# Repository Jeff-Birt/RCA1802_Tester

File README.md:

# RCA1802_Tester
Using an Aruino Mega 2560 to test RCA/Harris/Intersil 1802 processors

I boughtt a batch of old RCA 1802 micro-processors from C.H. Ina & Company on eBay. When they showed up it was obvious that had been sanded and re-labeled. The rest of the parts for the project I wanted them for had not arrived and I wanted to test them before complaining.

I had an Arduino Mega 2560 sitting on the bench and thought I would try to use it to test the 1802s. This project is the result of that effort...

NOTE:
 PCB Design, button handling code, and EF randomization code from: Hans Liss, Thanks Hans!

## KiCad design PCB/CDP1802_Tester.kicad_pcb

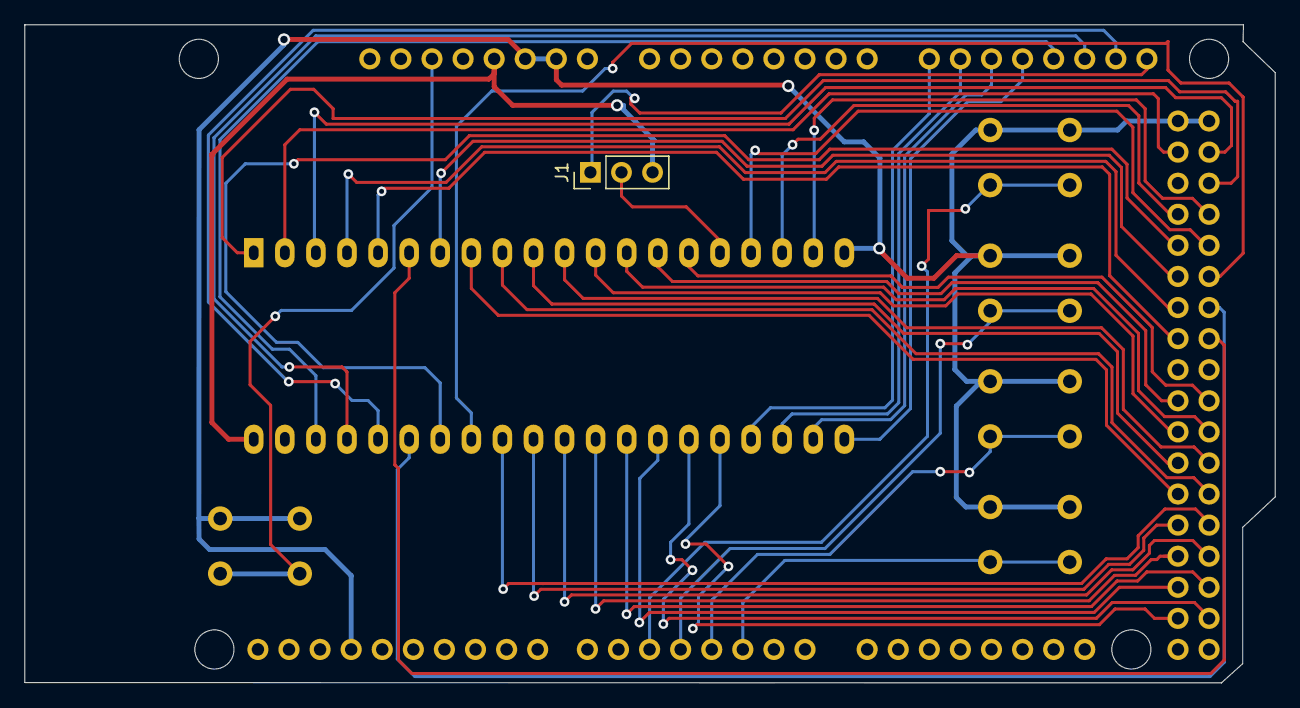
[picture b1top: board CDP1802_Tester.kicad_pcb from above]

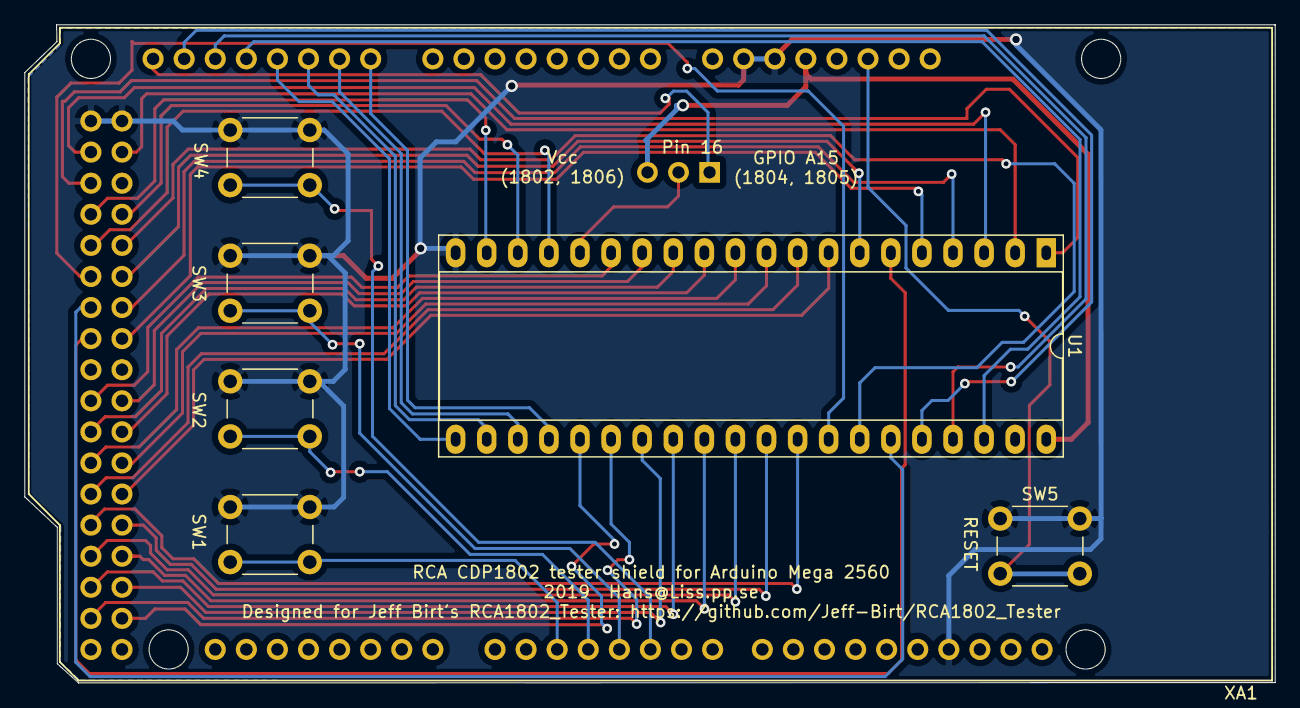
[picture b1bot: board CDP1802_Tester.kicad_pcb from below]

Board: 2 copper layers, 102.2 x 53.8 mm, 8 parts (7 on the bottom side), 45 nets.

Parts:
J1: Conn_01x03; Pin_Header_Straight_1x03_Pitch2.54mm
SW1, SW2, SW3, SW4, SW5: SW_Push; SW_PUSH_6mm
U1: CDP1802ACE; DIP-40_W15.24mm_Socket_ZIF
XA1: Arduino_Mega2560_Shield_alt1

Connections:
/CLEAR: U1.3, XA1.D53
/CLOCK: U1.1, XA1.D51
/D0: U1.15, XA1.D37
/D1: U1.14, XA1.D36
/D2: U1.13, XA1.D35
/D3: U1.12, XA1.D34
/D4: U1.11, XA1.D33
/D5: U1.10, XA1.D32
/D6: U1.9, XA1.D31
/D7: U1.8, XA1.D30
/DMA_IN: U1.38, XA1.A12
/DMA_OUT: U1.37, XA1.A13
/EF1: U1.24, XA1.A8
/EF2: U1.23, XA1.A9
/EF3: U1.22, XA1.A10
/EF4: U1.21, XA1.A11
/INTERRUPT: U1.36, XA1.A14
/MA0: U1.25, XA1.D22
/MA1: U1.26, XA1.D23
/MA2: U1.27, XA1.D24
/MA3: U1.28, XA1.D25
/MA4: U1.29, XA1.D26
/MA5: U1.30, XA1.D27
/MA6: U1.31, XA1.D28
/MA7: U1.32, XA1.D29
/MRD: U1.7, XA1.D44
/MWR: U1.35, XA1.D43
/N0: U1.19, XA1.D49
/N1: U1.18, XA1.D48
/N2: U1.17, XA1.D47
/Q: U1.4, XA1.D42
/SC0: U1.6, XA1.D41
/SC1: U1.5, XA1.D40
/TPA: U1.34, XA1.D46
/TPB: U1.33, XA1.D45
/WAIT: U1.2, XA1.D52
GND: SW1.2, SW2.2, SW3.2, SW4.2, SW5.1, U1.20, XA1.GND1, XA1.GND2, XA1.GND3, XA1.GND5, XA1.GND6
unnamed: J1.1, XA1.A15
unnamed: J1.2, U1.16
unnamed: SW1.1, XA1.D2
unnamed: SW2.1, XA1.D3
unnamed: SW3.1, XA1.D4
unnamed: SW4.1, XA1.D5
unnamed: SW5.2, XA1.RST1
VCC: J1.3, U1.40, XA1.5V1

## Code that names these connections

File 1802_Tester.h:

#pragma once

// PORT A (inputs to Arduino)
#define ADD_BUS		0xFF	// well, the address bus of course

// PORT B (Outputs from Arduino)
// /CLEAR	/WAIT	MODE (1802)
//	L		L		LOAD
//	L		H		RESET
//	H		L		PAUSE
//	H		H		RUN
#define CLEAR		0x01	// active low
#define WAIT		0x02	// active Low
#define CLOCK		0x04	// Clock input, active low

// PORT C (bi-directional)
#define DATA_BUS	0xFF	// well, the data bus of course

//PORT G (inputs to Arduino)
#define SC0			0x01	// SC0==0->Fetch, SC0==1->Execute
#define SC1			0x02	// 

// PORT K (Outputs from Arduino)
#define EF1			0x01	// EF1 Input
#define EF2			0x02	// EF2 Input
#define EF3			0x04	// EF3 Input
#define EF4			0x08	// EF4 Input
#define DMA_IN		0x10	// DMA Input mode flag
#define DMA_OUT		0x20	// DMA Output mode flag
#define INTERRUPT	0x40	// Interrupt input
#define PIN16 		0x80	// Pin 16 on an 1804

// PORT L (inputs to Arduino)
#define N0			0x01	// I/O Control Line 0
#define N1			0x02	// I/O Control Line 1
#define N2			0x04	// I/O Control Line 2
#define TPA			0x08	// Timing Pulse A, MSB of address
#define TPB			0x10	// Timing Pulse B, LSB of address
#define MRD			0x20	// Memory Read, active low
#define MWR			0x40	// Memory Write, active low
#define Q			0x80	// Q flip-flop output

#define BTN1 5				// buttons included on shield
#define BTN2 4				// these are Arduino pin numbers
#define BTN3 3
#define BTN4 2

void stateDecode();				// decode control signal state (rising/falling/steady) 
void cmdDecode(String command);	// decodes commands from serial port
void logState(String note);		// helper to dump current state out to serial port
void portC_ModeInput(void);		// set data bus to HIZ input mode
byte portC_InputValue(void);	// input byte from data bus
void portC_ModeOutput(void);	// set data bus to output mode
void portC_OutputValue(byte value); // output a byte on the data bus
String intToHex(int value, int places);	// convert int to hex padded #places

const int buttons[] = { BTN1, BTN2, BTN3, BTN4 };
#define NBUTTONS (sizeof(buttons)/sizeof(int))
int buttonState[NBUTTONS];
boolean isButtonRead[NBUTTONS];
int lastButtonState[NBUTTONS];
int lastDebounceTime[NBUTTONS];

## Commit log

2019-11-14 Can now run simple programs. Included a simple Q blink program.
    Still need to wire up N0-N2, EF1-EF4 and write 1802 code to test them.
2019-11-17 Have working virtual memory read and write. Also have I/O Output working. Need a way to dump virtual memory to check after a write.
2019-11-17 Have Input from I/O working now. Need to rework how the data bus direction is changed on the Arduino.
2019-11-17 Cleaned up the control signal state decoding and started on making the debug output adjustable.
2019-11-18 Have basic serial input command structure working. Can start, stop, dump virtual memory, etc.
2019-11-24 Last commit before publishing video, all serial commands tested and working
2020-01-10 Added button code Fixed PORTK initialization bug
2020-01-10 Added PCB KiCad project
2020-01-10 Added Device and Footprint libraries for the modified shield
2020-01-12 Merged in changes from Hans Liss and reformatted them slightly. Updated ReadMe to thank Hans.
2020-04-15 Changed ZIF socket to wide (oval) pins Added jumper for pin 16 to either Vcc or A15 on the Arduino Added Reset button Set A15/PIN16 to OUTPUT and default HIGH Updated code to use SW3 to toggle the va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
